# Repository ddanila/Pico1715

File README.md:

# Pico1715

An independent Pico-based replacement/expansion card for the Robotron PC 1715:
SD-backed virtual floppies, external RAM and a buffered X2 bus interface.
Original project code and design files are MIT licensed; see [LICENSE](LICENSE).

Configurable [compact triggers and rolling history](docs/analyzer-triggers.md) now
support event/address/data matching, bounded pre/post windows and USB download.

## Status

The scheduled-byte card model boots the unchanged classic ROM into SCP 0006 and
passes nine software regressions plus 36 latency/fault experiments.
See the [timing results](docs/timing-contract.md) and
[hardware requirements derived from them](hardware/timing-requirements.md).
The FPGA normal-I/O and interrupt frontend now passes all nine ROM/OS cases
in RTL co-simulation, including a shared-firmware profile with journaled SD
writeback. A 59-pin Olimex HX8K bench target is placed and routed,
and Pico Plus 2 firmware builds with PSRAM, SD CRC checking and optional journaled
writeback. See the [prototype build, wiring and parts guide](hardware/prototype.md).

**Bench prototype, not ready to manufacture:** no firmware has run on hardware,
no X2 electrical measurements have been made, and no qualified PCB exists.
The firmware co-simulator compiles the same service loop and journal code for
host execution and connects them to the board-level RTL. GPIO, time, PSRAM and
SD blocks are simulated; this does not execute RP2350 instructions or qualify
physical timing. See [firmware co-simulation](docs/firmware-cosim.md) and
[delayed storage, reset and recovery qualification](docs/firmware-storage-faults.md).

The standalone [analyzer transport](docs/analyzer-transport.md) now joins passive
FPGA cycle capture to a CRC-protected Pico link and a bounded 7 MiB PSRAM buffer.
Shared-firmware/RTL tests cover stalls, corruption, retry and buffer exhaustion;
stock-boot replay retains all 215,848 selected records. [USB control/download](docs/analyzer-usb.md)
now provides explicit arm/stop and validated capture files through a Python host
utility. A separate [passive analyzer adapter](hardware/analyzer-interface/README.md)
now has a checked schematic, full input harness and routed HX8K bitstream.
A [combined carrier schematic](hardware/carrier/README.md) now provides one
wiring contract for both personalities, a physical passive-mode interlock,
Pico power isolation, SD and button/SAFE-LED support. Both new FPGA targets route
with passing internal timing. Physical assembly, USB/timing qualification and
PCB layout remain open.

An experimental third [combined controller/capture personality](docs/combined-mode.md)
now runs disk service and finite analyzer capture concurrently. Classic CP/M guest
write/cold-read tests preserve existing files, and the HX8K build meets its
internal clock constraints. Capture loss under load is explicitly reported.
The optional [reserve supervisor](docs/reserve-interface.md) uses PIM724 SP/CE
GPIO32/33/36 and defaults to zero qualified energy. See the
[Rev A order gates](docs/rev-a-release.md) for remaining PCB work.

The first compatibility target is the **ordinary PC 1715**, retaining its boot
ROM and operating-system floppy routines. It must not be confused with the
**1715W/M**: the existing DAC emulator and available S550/TOS/M reference boot
exercise the latter's 8272-based controller. They are useful infrastructure,
not evidence that the ordinary 1715 controller has been implemented.
The owner's MB001 inventory identifies an ordinary 1715. Its board revision,
connector orientation and electrical behavior still require physical verification.

## Run the existing emulator baseline

Requirements: Python 3.10+, a C11 compiler, Git, and the external
[dac-emulation](https://github.com/ddanila/dac-emulation) checkout at the revision
recorded in [sources.json](docs/sources.json). No Python packages are required.

```sh
python3 tools/capture_dac.py \
  --dac ../dac-emulation \
  --rom ../dac/public/media/robotron/s550.bin \
  --prom ../dac/public/media/robotron/cas.bin \
  --disk ../dac/public/media/robotron/tosm10.img \
  --out local/wm-baseline
python3 -m unittest discover -s tests -v
```

The tool builds its adapter and the external emulator in this project's ignored
`build/` directory. It requires the pinned revision and clean tracked dependency
files. Inputs are read-only; the output directory must not already exist.
It records input hashes, emulator identity, I/O and interrupt-acknowledge events,
a text screen, and a report. It exits unsuccessfully if the boot prompt is absent,
inputs change, or the trace is truncated. ROM and disk contents are not committed.
Even the local trace can contain guest data: it stays ignored by default.

This is an **observational W/M baseline**, not co-simulation with Pico1715.
Read/write events can repeat on consecutive emulated CPU ticks; they are not
necessarily distinct bus transactions. Timestamps are emulator scheduling ticks,
not qualified physical X2 signal edges.

[Controller USB](docs/controller-usb.md) provides status and safe eject without
a debugger, including initialization/storage diagnostics and a host CLI.

## Next milestones

The [roadmap](docs/roadmap.md) separates implemented desk work from hardware
qualification. Safe eject/reserve-aware shutdown, motherboard interrupt-chain
modelling, firmware cost/fault tests, and controller USB status/eject are implemented
and tested within their documented simulation limits.

Analyzer capture, filtering, triggers, PSRAM transport, USB download and decoding
are also implemented. The [combined carrier](hardware/carrier/README.md) has checked
controller/analyzer FPGA personalities and a physical passive-mode interlock.
[Remote-reset software](docs/analyzer-reset.md) exists for the optional standalone
accessory; that accessory remains electrically unqualified and is disabled on the
combined carrier because GP22 serves SD chip select. X1/X2's reset contact alone
does not reset the CPU on the documented motherboard.

The [carrier layout](hardware/carrier/mechanics.md) now has local bypass placement,
2,206 routed segments, 426 vias and ground pours on both copper layers. All placed
non-SD terminals are connected. KiCad DRC reports zero violations and **12 open
connections, all involving the held SD socket**. X2 remains unplaced. See the
[routing evidence](hardware/carrier/routing.md). This is not a fabrication release;
SD/X2 geometry, return-path and timing review, optional backup power, broader OS
coverage and physical tests remain open.

Physical milestones remain:

1. Assemble the selected bench modules and verify PSRAM, SD and FPGA programming.
2. Measure worst-case Pico mailbox latency and translated bus timing on a fixture.
3. Verify X2 orientation, priority-chain wiring and mechanics on the actual 1715;
   boot the unchanged ROM and repeat the read/write/persistence tests.
4. Freeze the schematic, route the PCB, run ERC/DRC, and review manufacturing
   outputs; qualify assembled prototypes before declaring RTM.

See [hardware requirements](hardware/requirements.md),
[modelling plan](docs/modelling.md), [classic controller contract](docs/classic-controller.md)
and [licensing/provenance](NOTICE.md). The initial passing W/M run is recorded in
[reports/wm-baseline.json](reports/wm-baseline.json); local reference identities
are listed in [docs/local-evidence.json](docs/local-evidence.json).

## Plain PC1715 model

The pinned DAC revision supplies `machines/robotron1715` (runtime kind 3) with
64 KB RAM, the original ROM overlay and native card callbacks. This repository's
`model/controller.c` attaches to it without changing the emulator or guest code.
The runner enables onboard CTC/SIO, feeds completed keyboard bytes into the SIO
receive FIFO and reads the text screen from RAM. See the
[stock-software qualification](docs/onboard-keyboard.md). Production firmware
uses a bounded [two-byte receive queue](docs/receive-elasticity.md) to handle
index/mark interrupt overlap; the standalone reference model defaults to one byte.
[Service-cost tests](docs/service-costs.md) now cover processing stalls, shared-lock
contention, watchdog release and recovery during SD writeback.
[Stock Z80 cost experiments](docs/cpu-service-costs.md) combine these delays with
boot, BDOS and persistence checks, preserving both passing and overloaded profiles.
[Receive read-ahead](docs/read-ahead.md) moves byte preparation into idle mailbox
time while retaining the same two-byte capacity.
[Transmit staging](docs/transmit-staging.md) acknowledges bounded byte capture
before processing, preserving serializer deadlines and CRC validation.
[Combined stress](docs/combined-stress.md) adds deterministic processing bursts,
variable SD write latency and index-interrupt offsets, with overload and remount checks.
[Interrupt fault isolation](docs/interrupt-fault-isolation.md) releases failed
controller IRQ ownership and bypasses the chain until reset.

```sh
make test
python3 tools/check_classic.py \
  --dac ../dac-emulation \
  --rom /path/r1715bt.bin \
  --disk /path/r1715.cpm \
  --out local/classic-check
```

The checker requires the ROM and SCP image hashes recorded in
[local-evidence.json](docs/local-evidence.json), and a fresh output directory.
Inputs are read-only; writes affect disposable copies. It tests original-image
boot/DIR, SAVE, persistence, a disk-loaded BDOS read/write workload, TYPE after
cold boot, deletion/persistence, write protection, and absent media. Model-only
contract tests also cover malformed writes and interrupt/reset behavior.

See [reports/classic-compatibility.json](reports/classic-compatibility.json) and
[the controller contract and remaining gaps](docs/classic-controller.md).
Use `--timed` for scheduled bytes, or `tools/check_timing.py` with the same
arguments for the full timing suite.
**Scheduled bytes are not an electrically qualified hardware design.** Generic
PIO modes, full motherboard peripherals, other formats and physical bus behavior
remain outside this qualification.

## Bench adapter and fixture

The [buffered adapter schematic](hardware/interface/README.md) includes hardware
output gating and dual-rail supervision. The [standalone FPGA/Pico fixture](hardware/bench-fixture.md)
checks 515 mailbox transactions, IRQ/vector/RETI and returns a UART result.
Both are bench artifacts: [X2 common contacts](hardware/x2-pinout.md) are now
source-checked and assigned, including original-controller IRQ direction. Physical
validation and connector footprint selection remain pending.

The [four-contact EFS test fixture](hardware/efs58-coupon/README.md) provides
printed holder STL/STEP files, a routed passive breakout PCB and fabrication
files. It lets us screen a modern loose socket before committing to a full
58-contact replacement. Mating fit still requires sacrificial-contact trials.

## Prototype validation

```sh
make test test-store test-frontend test-irq test-pico-top lint-frontend
python3 tools/check_classic.py --cosim --dac ../dac-emulation \
  --rom /path/r1715bt.bin --disk /path/r1715.cpm --out local/rtl-check
```

RTL co-simulation requires Verilator and a C++ compiler. See
[reports/rtl-compatibility.json](reports/rtl-compatibility.json) for the nine-case
result and source hashes, and [the prototype guide](hardware/prototype.md) for
FPGA and firmware builds. ROMs and disk images remain external.

The [classic 1715 trace decoder](docs/analyzer-decoder.md) provides controller
timelines, field CRC checks, configurable WAIT/gap diagnostics and reference
comparison for downloaded compact captures.

[Safe eject and shutdown](docs/shutdown.md) now drain the journal before reporting
safe, with optional reserve-gated writeback and deterministic outage tests.

[Motherboard interrupt-chain tests](docs/motherboard-interrupts.md) now exercise
the real controller with CTC/SIO priority, IM2 vectors, RETI and card isolation.

The latest [desk-work pass](docs/desk-completion.md) adds a provisional routed
58-contact X2 breakout, assembly/probe documentation, return-path screening with
23 extra ground stitches, and a 30-case external-media survey/persistence suite.
The separate [four-layer Rev A](hardware/carrier-reva/README.md) now uses the
drawing-checked Würth SD socket and host header, with zero ERC/DRC violations
and zero opens. Return-path closure, final manufacturing review, actual connector
fit and hardware qualification remain open.

Further desk work now includes [W-loader diagnosis](docs/boot-image-diagnosis.md),
[indexed multi-extent and disk-full tests](docs/pattern-media.md) on native and
shared-firmware/FPGA backends, and an [optional reserve-power schematic](hardware/backup-power/README.md).
The reserve remains a draft with no GPIO integration or measured hold-up guarantee.

The [browser workstation](docs/browser-workstation.md) builds model and firmware/RTL
WebAssembly sessions for the classic-1715 DAC museum exhibit.

[Session capture](docs/session-capture.md) connects both emulator backends to the
workbench. The [guided bring-up runner](docs/bringup-runner.md) collects staged,
hash-bound evidence; simulated rehearsal never qualifies hardware.

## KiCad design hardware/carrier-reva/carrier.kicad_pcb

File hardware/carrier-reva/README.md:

# Rev A carrier engineering candidate

**Not for fabrication or connection to a 1715.** This directory is a separate
four-layer development candidate. The reviewed two-layer baseline remains in
`../carrier`. No physical validation is claimed.

The electrical ECO replaces the unplaced X2 schematic symbol with J6, a 60-pin
2.54 mm keyed IDC header candidate, and adds J7 for optional reserve power.
All 76 schematic components are placed. ERC and DRC are checked afresh by the
CAD target. The SD socket is now Würth 693071010811, with all connections closed.
J6 uses the exact 61206021621 drawing dimensions, including 1.10 mm holes.
J7's 0.95 mm finished holes match the JST 0.90–1.00 mm reference range.
See `sd-replacement-review.md` and `connector-review.json` for sources and limits.
Drawing checks do not claim physical fit or signal-integrity qualification.

## Harness and power

Use a straight-through keyed 60-conductor cable, maximum 100 mm, to a separate
EFS58 adapter. The **electrical** assignment is A1→1, B1→2, … A29→57,
B29→58; pins 59 and 60 are NC. Every contact, including existing unused
contacts, is in `connections.json`. This mapping is not a claim about the
EFS contact fit. J6 top-view pin 1 is at (60,215), pin 2 at
(60,212.46); the key faces south, toward the odd row. The mate-facing view
is mirrored: assemble by pin numbers and verify continuity before use. Do not infer orientation
from a mirrored photograph or wire-colour convention.

J7 is a power connector, not a status/GPIO port:

| Pin | Net | Function |
| --- | --- | --- |
| 1 | GND | Common return |
| 2 | V5_MODULE | Raw module supply |
| 3 | P_VSYS | Backed Pico supply |

Keep D1 fitted. Leave J7 empty for the initial assembly; the reserve daughterboard
is not included in the first order. Never jumper pins 2 and 3 as an improvised
reserve bypass. The normal D1 feed already supports operation without reserve.
Reserve status uses Pico SP/CE GP32/33/36 separately; the firmware supervisor
must not report a protected write budget without measured hold-up evidence.

## Layout and validation

The candidate is 160 × 210 mm. F.Cu/B.Cu carry signals and power; In1.Cu/In2.Cu
are GND. The proposed 1.6 mm ENIG stack-up targets JLC04161H-7628 but remains
subject to supplier confirmation. The SD body exclusion applies only to F.Cu.
Existing outer copper is retained; the routing workflow defaults to removing
F_CLK and F_WR_N for re-routing and adds the host/reserve connections. Repeat
`--replace-net NET` to select other nets without disturbing previously replaced
routes. Router output is
never itself sign-off evidence.

- `make test-carrier-reva`: portable net parity and interface mutation tests.
- `make test-carrier-reva-cad`: fresh schematic export, ERC and DRC review.
  It explicitly permits and **reports** open connections; it is not an order gate.
- `python3 tools/package_carrier_reva.py --out local/reva-review-<unique-name>`:
  freshly checked, hashed engineering review ZIP. No order Gerbers are included.
- `/usr/bin/python3 tools/prepare_carrier_reva_routing.py --out local/reva-router`:
  outer-layer router input with SD present and ground excluded.
- `/usr/bin/python3 tools/import_carrier_reva_routing.py local/reva-router local/reva-routes.json`:
  candidate additions from `carrier.ses`; import into the generator with
  `--routes`, then refill/check independently before adoption.

Regenerate the schematic with `python3 tools/generate_carrier_reva.py`, export
its netlist with KiCad's `kicadxml` format, then generate the PCB with
`/usr/bin/python3 tools/generate_carrier_reva_pcb.py`. The board generator needs
KiCad 10's system Python module. It uses the checked-in `routes.json` by default. `--base-only` explicitly
creates the uncompleted placement candidate. `--routes` selects a different
candidate for review. The checked `placement-overrides.json` moves only C19;
connector/module positions and mounting holes stay fixed.

All 408 signal vias now meet the 4 mm return target, and planar assembly/plane
gap desk review is recorded in `assembly-review.json`. A fabrication release
has independently inspected exports bound by hashes; release still requires supplier acceptance and a
postcode-specific delivered Estonia quote. Physical EFS fit, power isolation, signal integrity and functional
bring-up remain later gates. Assemble and test one board before populating four
more. CPU RESET2 remains an input, not a board-driven CPU reset output.

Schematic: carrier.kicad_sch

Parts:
C1, C2, C3, C4, C5, C6, C7, C8, C9, C10, C11, C12, C13, C14, C15, C16, C17, C18, C19: 100nF; C_0805_2012Metric
C20, C21, C22: 10uF_10V; C_0805_2012Metric
D1: SS14; D_SMA
EXT1: OLIMEX_EXT1; PinHeader_2x20_P1.27mm_Vertical
EXT2: OLIMEX_EXT2; PinHeader_2x20_P1.27mm_Vertical
EXT3: OLIMEX_EXT3; PinHeader_2x20_P1.27mm_Vertical
ISO1, ISO2, ISO3: SN74CB3Q3245PWR; TSSOP-20_4.4x6.5mm_P0.65mm
J1: PGM1_PIN5_CDONE_TAP; PinHeader_1x02_P2.54mm_Vertical
J2: PIM724_PICO_PLUS2; PIM724_SocketPair
J3: 693071010811; microSD_Wuerth_693071010811
J4: REGULATED_5V_INPUT; JST_XH_B2B-XH-A_1x02_P2.50mm_Vertical
J5: BRINGUP_PROBES; PinHeader_1x15_P2.54mm_Vertical
J6: 61206021621_HOST_HARNESS; IDC_Wuerth_61206021621
J7: B3B-XH-A_RESERVE_POWER; JST_XH_B3B-XH-A_1x03_P2.50mm_Vertical
R1, R3, R5: 2k2; R_0805_2012Metric
R2, R4, R6: 22k; R_0805_2012Metric
R7, R8, R9, R10, R11, R12, R13, R17, R19, R20, R21: 4k7; R_0805_2012Metric
R14, R15: 1k; R_0805_2012Metric
R16: 100k; R_0805_2012Metric
R18: 10k; R_0805_2012Metric
R22, R23, R24: 47k; R_0805_2012Metric
RX1, RX2, RX3, RX4, RX5: SN74LVC541ADWR; SOIC-20W_7.5x12.8mm_P1.27mm
SW1: JS202011JCQN; JS202011JCQN_VendorPins
U4: SN74AHCT541DWR; SOIC-20W_7.5x12.8mm_P1.27mm
U5: SN74AHCT1G125DBVR; SOT-23-5
U6, U7: SN74LVC08ADR; SOIC-14_3.9x8.7mm_P1.27mm
U8, U13: SN74LVC00ADR; SOIC-14_3.9x8.7mm_P1.27mm
U9: SN74LVC07ADR; SOIC-14_3.9x8.7mm_P1.27mm
U10, U12: TLV803EA30DBZR; SOT-23
U11: TLV803EA46DBZR; SOT-23

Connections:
/ARMED: J5.9 (ARMED), U7.11 (4Y), U8.1 (1A), U8.4 (2A), U8.9 (3A), U8.12 (4A), U8.13 (4B)
/BACKEND_OK: U7.6 (2Y), U7.9 (3A)
/CDONE: J1.1 (CDONE_FROM_PGM1_5), J5.5 (CDONE), R16.1, U6.10 (3B)
/DATA_EN_N: U8.3 (1Y), U9.1 (1A)
/DATA_OE_N: J5.10 (DATA_OE_N), R14.2, U4.19 (OE2_N), U9.2 (1Y)
/DRIVEN_IEO: SW1.7 (CONTROLLER_IEO), U5.4 (Y)
/F_A0: EXT1.7 (F_A0), RX1.18 (Y0)
/F_A1: EXT1.9 (F_A1), RX1.17 (Y1)
/F_A2: EXT1.11 (F_A2), RX1.16 (Y2)
/F_A3: EXT1.13 (F_A3), RX1.15 (Y3)
/F_A4: EXT1.15 (F_A4), RX1.14 (Y4)
/F_A5: EXT1.17 (F_A5), RX1.13 (Y5)
/F_A6: EXT1.19 (F_A6), RX1.12 (Y6)
/F_A7: EXT1.21 (F_A7), RX1.11 (Y7)
/F_A8: EXT2.15 (F_A8), RX2.18 (Y0)
/F_A9: EXT2.17 (F_A9), RX2.17 (Y1)
/F_A10: EXT2.19 (F_A10), RX2.16 (Y2)
/F_A11: EXT2.21 (F_A11), RX2.15 (Y3)
/F_A12: EXT2.23 (F_A12), RX2.14 (Y4)
/F_A13: EXT2.25 (F_A13), RX2.13 (Y5)
/F_A14: EXT2.27 (F_A14), RX2.12 (Y6)
/F_A15: EXT2.29 (F_A15), RX2.11 (Y7)
/F_BAO_N: EXT2.40 (F_BAO_N), RX5.15 (Y3)
/F_BUSRQ_N: EXT2.39 (F_BUSRQ_N), RX5.16 (Y2)
/F_CLK: EXT2.33 (F_CLK), RX4.12 (Y6)
/F_D0: EXT1.23 (F_D0), RX3.18 (Y0)
/F_D1: EXT1.25 (F_D1), RX3.17 (Y1)
/F_D2: EXT1.27 (F_D2), RX3.16 (Y2)
/F_D3: EXT1.29 (F_D3), RX3.15 (Y3)
/F_D4: EXT1.31 (F_D4), RX3.14 (Y4)
/F_D5: EXT1.33 (F_D5), RX3.13 (Y5)
/F_D6: EXT1.35 (F_D6), RX3.12 (Y6)
/F_D7: EXT1.37 (F_D7), RX3.11 (Y7)
/F_DO0: EXT1.39 (F_DO0), U4.2 (A0)
/F_DO1: EXT1.40 (F_DO1), U4.3 (A1)
/F_DO2: EXT1.38 (F_DO2), U4.4 (A2)
/F_DO3: EXT1.36 (F_DO3), U4.5 (A3)
/F_DO4: EXT1.34 (F_DO4), U4.6 (A4)
/F_DO5: EXT1.32 (F_DO5), U4.7 (A5)
/F_DO6: EXT1.30 (F_DO6), U4.8 (A6)
/F_DO7: EXT1.28 (F_DO7), U4.9 (A7)
/F_FAULT: EXT2.13 (F_FAULT), J5.13 (F_FAULT)
/F_HOST_OE: EXT1.10 (F_HOST_OE), R10.1, U8.2 (1B)
/F_IEO: EXT2.11 (F_IEO), R13.1, U5.2 (A)
/F_INT: EXT2.9 (F_INT), R12.1, U8.10 (3B)
/F_INT_N: EXT2.37 (F_INT_N), RX5.17 (Y1)
/F_IORQ_N: EXT1.26 (F_IORQ_N), RX4.17 (Y1)
/F_M1_N: EXT1.24 (F_M1_N), RX4.14 (Y4)
/F_MREQ_N: EXT1.22 (F_MREQ_N), RX4.18 (Y0)
/F_PRIORITY: EXT1.16 (F_PRIORITY), RX5.14 (Y4)
/F_RD_N: EXT1.20 (F_RD_N), RX4.16 (Y2)
/F_RESET_N: EXT1.14 (F_RESET_N), ISO2.9 (A7), RX4.11 (Y7), U7.10 (3B)
/F_RFSH_N: EXT2.31 (F_RFSH_N), RX4.13 (Y5)
/F_WAIT: EXT2.7 (F_WAIT), R11.1, U8.5 (2B)
/F_WAIT_N: EXT2.35 (F_WAIT_N), RX5.18 (Y0)
/F_WR_N: EXT1.18 (F_WR_N), RX4.15 (Y3)
/GND: C1.2, C2.2, C3.2, C4.2, C5.2, C6.2, C7.2, C8.2, C9.2, C10.2, C11.2, C12.2, C13.2, C14.2, C15.2, C16.2, C17.2, C18.2, C19.2, C20.2, C21.2, C22.2, EXT1.2 (GND), EXT1.4 (GND), EXT1.8 (GND), EXT2.2 (GND), EXT2.4 (GND), EXT2.8 (GND), EXT3.2 (GND), EXT3.4 (GND), EXT3.8 (GND), ISO1.10 (GND), ISO2.10 (GND), ISO3.10 (GND), J1.2 (GND), J2.3 (GND), J2.8 (GND), J2.13 (GND), J2.18 (GND), J2.23 (GND), J2.28 (GND), J2.33 (GND), J2.38 (GND), J3.6 (VSS), J4.2 (GND), J5.1 (GND), J6.1 (0V), J6.2 (0V), J6.3 (0V), J6.4 (0V), J7.1 (GND), R2.2, R4.2, R6.2, R7.2, R8.2, R9.2, R10.2, R11.2, R12.2, R13.2, R16.2, R19.2, R20.2, RX1.1 (OE1_N), RX1.10 (GND), RX1.19 (OE2_N), RX2.1 (OE1_N), RX2.10 (GND), RX2.19 (OE2_N), RX3.1 (OE1_N), RX3.10 (GND), RX3.19 (OE2_N), RX4.1 (OE1_N), RX4.10 (GND), RX4.19 (OE2_N), RX5.1 (OE1_N), RX5.7 (A5), RX5.8 (A6), RX5.9 (A7), RX5.10 (GND), RX5.19 (OE2_N), SW1.1 (PASSIVE_GND), U4.1 (OE1_N), U4.10 (GND), U5.3 (GND), U6.7 (GND), U7.7 (GND), U8.7 (GND), U9.7 (GND), U10.1 (GND), U11.1 (GND), U12.1 (GND), U13.4 (2A), U13.5 (2B), U13.7 (GND), U13.9 (3A), U13.10 (3B), U13.12 (4A), U13.13 (4B)
/H_A0: J6.37 (AB0), RX1.2 (A0)
/H_A1: J6.38 (AB1), RX1.3 (A1)
/H_A2: J6.35 (AB2), RX1.4 (A2)
/H_A3: J6.36 (AB3), RX1.5 (A3)
/H_A4: J6.33 (AB4), RX1.6 (A4)
/H_A5: J6.34 (AB5), RX1.7 (A5)
/H_A6: J6.31 (AB6), RX1.8 (A6)
/H_A7: J6.32 (AB7), RX1.9 (A7)
/H_A8: J6.27 (AB8), RX2.2 (A0)
/H_A9: J6.28 (AB9), RX2.3 (A1)
/H_A10: J6.25 (AB10), RX2.4 (A2)
/H_A11: J6.26 (AB11), RX2.5 (A3)
/H_A12: J6.23 (AB12), RX2.6 (A4)
/H_A13: J6.24 (AB13), RX2.7 (A5)
/H_A14: J6.21 (AB14), RX2.8 (A6)
/H_A15: J6.22 (AB15), RX2.9 (A7)
/H_BAO_N: J6.53 (/BAO), RX5.5 (A3)
/H_BUSRQ_N: J6.40 (/BUSRQ), RX5.4 (A2)
/H_CLK: J6.41 (TAKT-X2), RX4.8 (A6)
/H_D0: J6.14 (DB0), RX3.2 (A0), U4.18 (Y0)
/H_D1: J6.13 (DB1), RX3.3 (A1), U4.17 (Y1)
/H_D2: J6.12 (DB2), RX3.4 (A2), U4.16 (Y2)
/H_D3: J6.11 (DB3), RX3.5 (A3), U4.15 (Y3)
/H_D4: J6.10 (DB4), RX3.6 (A4), U4.14 (Y4)
/H_D5: J6.9 (DB5), RX3.7 (A5), U4.13 (Y5)
/H_D6: J6.8 (DB6), RX3.8 (A6), U4.12 (Y6)
/H_D7: J6.7 (DB7), RX3.9 (A7), U4.11 (Y7)
/H_INT_N: J5.12 (H_INT_N), J6.46 (/INT), RX5.3 (A1), U9.6 (3Y)
/H_IORQ_N: J6.48 (/IORQ), RX4.3 (A1)
/H_M1_N: J6.51 (/M1), RX4.6 (A4)
/H_MREQ_N: J6.17 (/MREQ), RX4.2 (A0)
/H_PRIORITY: J6.20 (IEO), R18.2, RX5.6 (A4), SW1.5 (PASSIVE_IEI)
/H_PRIORITY_OUT: J6.19 (IEI), SW1.6 (COMMON_IEO)
/H_RD_N: J6.16 (/RD), RX4.4 (A2)
/H_RESET_N: J6.39 (/RESET), RX4.9 (A7)
/H_RFSH_N: J6.49 (/RFSH), RX4.7 (A5)
/H_WAIT_N: J5.11 (H_WAIT_N), J6.47 (/WAIT), RX5.2 (A0), U9.4 (2Y)
/H_WR_N: J6.15 (/WR), RX4.5 (A3)
/IEO_EN_N: U8.11 (4Y), U9.9 (4A)
/IEO_OE_N: R15.2, U5.1 (OE_N), U9.8 (4Y)
/INT_EN_N: U8.8 (3Y), U9.5 (3A)
/LINK_OE_N: ISO1.19 (OE_N), ISO2.19 (OE_N), ISO3.19 (OE_N), R17.2, U13.3 (1Y)
/LINK_OK: EXT3.29 (LINK_OK), J5.8 (LINK_OK), U6.8 (3Y), U6.13 (4B), U13.1 (1A), U13.2 (1B)
/L_GP0: EXT2.28 (L_GP0), ISO1.2 (A0)
/L_GP1: EXT2.26 (L_GP1), ISO1.3 (A1)
/L_GP2: EXT2.24 (L_GP2), ISO1.4 (A2)
/L_GP3: EXT2.22 (L_GP3), ISO1.5 (A3)
/L_GP4: EXT2.20 (L_GP4), ISO1.6 (A4)
/L_GP5: EXT2.18 (L_GP5), ISO1.7 (A5)
/L_GP6: EXT2.16 (L_GP6), ISO1.8 (A6)
/L_GP7: EXT2.14 (L_GP7), ISO1.9 (A7)
/L_GP8: EXT2.12 (L_GP8), ISO2.2 (A0)
/L_GP9: EXT2.10 (L_GP9), ISO2.3 (A1)
/L_GP10: EXT3.7 (L_GP10), ISO2.4 (A2)
/L_GP11: EXT3.9 (L_GP11), ISO2.5 (A3)
/L_GP12: EXT3.11 (L_GP12), ISO2.6 (A4)
/L_GP13: EXT3.13 (L_GP13), ISO2.7 (A5)
/L_GP14: EXT3.15 (L_GP14), ISO2.8 (A6), R19.1
/L_GP16: EXT3.17 (L_GP16), ISO3.2 (A0), R20.1
/L_GP17: EXT3.19 (L_GP17), ISO3.3 (A1), R21.1
/L_GP18: EXT3.21 (L_GP18), ISO3.4 (A2)
/L_GP19: EXT3.23 (L_GP19), ISO3.5 (A3)
/L_GP20: EXT3.25 (L_GP20), ISO3.6 (A4)
/L_GP21: EXT3.27 (L_GP21), ISO3.7 (A5), R9.1, U7.5 (2B)
/MODE_CTL: J5.6 (MODE_CTL), R7.1, SW1.2 (COMMON_MODE), U7.13 (4B)
/P3V3: C15.1, C19.1, C21.1, J2.36 (P3V3), J3.4 (VDD), J5.14 (P3V3), R5.1, R22.1, R23.1, R24.1, U12.3 (VDD)
/PERSONALITY_CTL: EXT2.38 (PERSONALITY_CTL), J5.7 (PERSONALITY_CTL), R8.1, U7.2 (1B)
/PG3: J5.2 (PG3), R1.2, R2.1, U6.1 (1A), U6.4 (2A), U10.2 (RESET_N)
/PG5: J5.3 (PG5), R3.2, R4.1, U6.2 (1B), U11.2 (RESET_N)
/PGP: J5.4 (PGP), R5.2, R6.1, U6.5 (2B), U12.2 (RESET_N)
/POWERED: U6.11 (4Y), U7.1 (1A)
/POWER_GOOD: EXT1.12 (POWER_GOOD), U6.3 (1Y), U6.12 (4A)
/P_GP0: ISO1.18 (B0), J2.1 (P_GP0)
/P_GP1: ISO1.17 (B1), J2.2 (P_GP1)
/P_GP2: ISO1.16 (B2), J2.4 (P_GP2)
/P_GP3: ISO1.15 (B3), J2.5 (P_GP3)
/P_GP4: ISO1.14 (B4), J2.6 (P_GP4)
/P_GP5: ISO1.13 (B5), J2.7 (P_GP5)
/P_GP6: ISO1.12 (B6), J2.9 (P_GP6)
/P_GP7: ISO1.11 (B7), J2.10 (P_GP7)
/P_GP8: ISO2.18 (B0), J2.11 (P_GP8)
/P_GP9: ISO2.17 (B1), J2.12 (P_GP9)
/P_GP10: ISO2.16 (B2), J2.14 (P_GP10)
/P_GP11: ISO2.15 (B3), J2.15 (P_GP11)
/P_GP12: ISO2.14 (B4), J2.16 (P_GP12)
/P_GP13: ISO2.13 (B5), J2.17 (P_GP13)
/P_GP14: ISO2.12 (B6), J2.19 (P_GP14)
/P_GP15: ISO2.11 (B7), J2.20 (P_GP15)
/P_GP16: ISO3.18 (B0), J2.21 (P_GP16)
/P_GP17: ISO3.17 (B1), J2.22 (P_GP17)
/P_GP18: ISO3.16 (B2), J2.24 (P_GP18)
/P_GP19: ISO3.15 (B3), J2.25 (P_GP19)
/P_GP20: ISO3.14 (B4), J2.26 (P_GP20)
/P_GP21: ISO3.13 (B5), J2.27 (P_GP21)
/P_GP22: J2.29 (P_GP22), J3.2 (DAT3_CS), R22.2
/P_GP26: J2.31 (P_GP26), J3.5 (CLK)
/P_GP27: J2.32 (P_GP27), J3.3 (CMD_MOSI)
/P_GP28: J2.34 (P_GP28), J3.7 (DAT0_MISO)
/P_VSYS: D1.1 (K), J2.39 (P_VSYS), J7.3 (BACKED_VSYS)
/QUALIFIED: U7.3 (1Y), U7.4 (2A)
/RAILS_OK: U6.6 (2Y), U6.9 (3A)
/RESET_OK: U7.8 (3Y), U7.12 (4A)
/SD_DAT1: J3.8 (DAT1), R23.2
/SD_DAT2: J3.1 (DAT2), R24.2
/V3P3: C1.1, C2.1, C3.1, C4.1, C5.1, C8.1, C9.1, C10.1, C11.1, C12.1, C13.1, C16.1, C17.1, C18.1, C20.1, EXT1.3 (V3P3), ISO1.20 (VCC), ISO2.20 (VCC), ISO3.20 (VCC), J5.15 (V3P3), R1.1, R17.1, R21.2, RX1.20 (VCC), RX2.20 (VCC), RX3.20 (VCC), RX4.20 (VCC), RX5.20 (VCC), SW1.3 (CONTROLLER_3V3), U6.14 (VCC), U7.14 (VCC), U8.14 (VCC), U9.11 (5A), U9.13 (6A), U9.14 (VCC), U10.3 (VDD), U13.14 (VCC)
/V5_HOST: C6.1, C7.1, C14.1, J6.57 (5P), J6.58 (5P), R3.1, R14.1, R15.1, R18.1, U4.20 (VCC), U5.5 (VCC), U11.3 (VDD)
/V5_MODULE: C22.1, D1.2 (A), EXT1.1 (V5_MODULE), J4.1 (5V), J7.2 (RAW_5V)
/WAIT_EN_N: U8.6 (2Y), U9.3 (2A)

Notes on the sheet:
Pico1715 Rev A / FOUR-LAYER CANDIDATE / NOT FOR FABRICATION
J6: straight-through 60-pin host harness; A=odd, B=even; 59/60 NC. Separate unqualified EFS58 adapter.
J7 reserve POWER only: 1 GND, 2 raw module 5V, 3 backed VSYS. Keep D1 fitted; optional daughter not included.
SD and connector drawing geometry checked; physical fit untested. RESET2 input only. Power off before mode or cable changes.

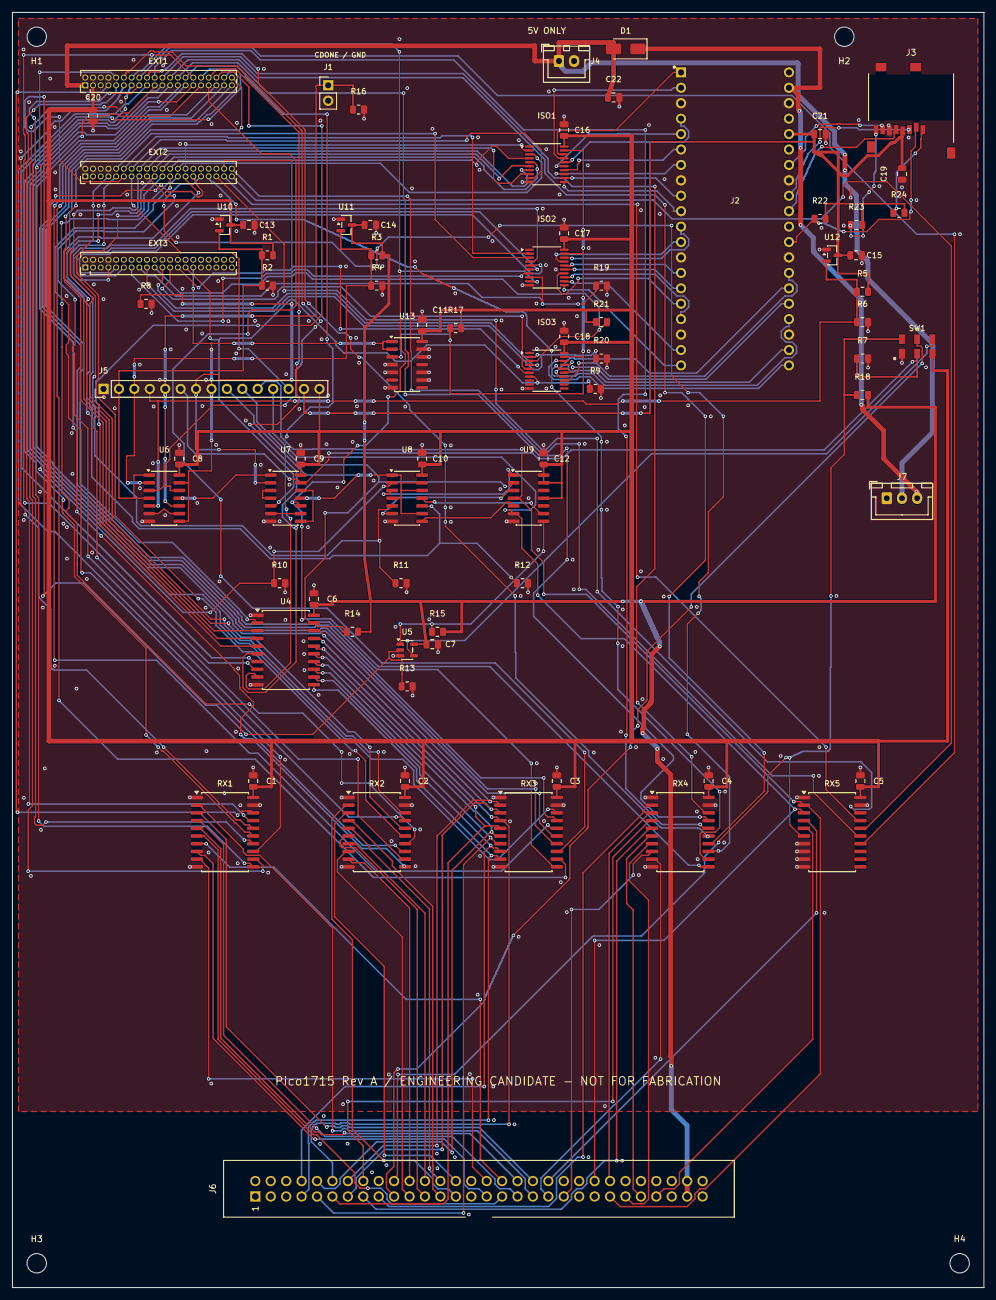
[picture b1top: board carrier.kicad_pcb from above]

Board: 4 copper layers, 160.0 x 210.0 mm, 80 parts (0 on the bottom side), 165 nets.

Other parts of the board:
H1, H2, H3, H4: MountingHole_3.2mm_M3

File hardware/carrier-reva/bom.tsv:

Reference	Value	Footprint	Datasheet
J6	61206021621_HOST_HARNESS	Pico1715_RevA:IDC_Wuerth_61206021621	https://www.we-online.com/components/products/datasheet/6120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
RX1	SN74LVC541ADWR	Package_SO:SOIC-20W_7.5x12.8mm_P1.27mm	https://www.ti.com/lit/ds/symlink/sn74lvc541a.pdf
RX2	SN74LVC541ADWR	Package_SO:SOIC-20W_7.5x12.8mm_P1.27mm	https://www.ti.com/lit/ds/symlink/sn74lvc541a.pdf
RX3	SN74LVC541ADWR	Package_SO:SOIC-20W_7.5x12.8mm_P1.27mm	https://www.ti.com/lit/ds/symlink/sn74lvc541a.pdf
RX4	SN74LVC541ADWR	Package_SO:SOIC-20W_7.5x12.8mm_P1.27mm	https://www.ti.com/lit/ds/symlink/sn74lvc541a.pdf
RX5	SN74LVC541ADWR	Package_SO:SOIC-20W_7.5x12.8mm_P1.27mm	https://www.ti.com/lit/ds/symlink/sn74lvc541a.pdf
U4	SN74AHCT541DWR	Package_SO:SOIC-20W_7.5x12.8mm_P1.27mm	https://www.ti.com/lit/ds/symlink/sn74ahct541.pdf
U5	SN74AHCT1G125DBVR	Package_TO_SOT_SMD:SOT-23-5	https://www.ti.com/lit/ds/symlink/sn74ahct1g125.pdf
U6	SN74LVC08ADR	Package_SO:SOIC-14_3.9x8.7mm_P1.27mm	https://www.ti.com/lit/ds/symlink/sn74lvc08a.pdf
U7	SN74LVC08ADR	Package_SO:SOIC-14_3.9x8.7mm_P1.27mm	https://www.ti.com/lit/ds/symlink/sn74lvc08a.pdf
U8	SN74LVC00ADR	Package_SO:SOIC-14_3.9x8.7mm_P1.27mm	https://www.ti.com/lit/ds/symlink/sn74lvc00a.pdf
U13	SN74LVC00ADR	Package_SO:SOIC-14_3.9x8.7mm_P1.27mm	https://www.ti.com/lit/ds/symlink/sn74lvc00a.pdf
U9	SN74LVC07ADR	Package_SO:SOIC-14_3.9x8.7mm_P1.27mm	https://www.ti.com/lit/ds/symlink/sn74lvc07a.pdf
U10	TLV803EA30DBZR	Package_TO_SOT_SMD:SOT-23	https://www.ti.com/lit/ds/symlink/tlv803e.pdf
U11	TLV803EA46DBZR	Package_TO_SOT_SMD:SOT-23	https://www.ti.com/lit/ds/symlink/tlv803e.pdf
U12	TLV803EA30DBZR	Package_TO_SOT_SMD:SOT-23	https://www.ti.com/lit/ds/symlink/tlv803e.pdf
SW1	JS202011JCQN	Pico1715_Carrier:JS202011JCQN_VendorPins	https://www.littelfuse.com/products/switches/slide-switches/js
ISO1	SN74CB3Q3245PWR	Package_SO:TSSOP-20_4.4x6.5mm_P0.65mm	https://www.ti.com/lit/ds/symlink/sn74cb3q3245.pdf
ISO2	SN74CB3Q3245PWR	Package_SO:TSSOP-20_4.4x6.5mm_P0.65mm	https://www.ti.com/lit/ds/symlink/sn74cb3q3245.pdf
ISO3	SN74CB3Q3245PWR	Package_SO:TSSOP-20_4.4x6.5mm_P0.65mm	https://www.ti.com/lit/ds/symlink/sn74cb3q3245.pdf
EXT1	OLIMEX_EXT1	Connector_PinHeader_1.27mm:PinHeader_2x20_P1.27mm_Vertical	-
EXT2	OLIMEX_EXT2	Connector_PinHeader_1.27mm:PinHeader_2x20_P1.27mm_Vertical	-
EXT3	OLIMEX_EXT3	Connector_PinHeader_1.27mm:PinHeader_2x20_P1.27mm_Vertical	-
J1	PGM1_PIN5_CDONE_TAP	Connector_PinHeader_2.54mm:PinHeader_1x02_P2.54mm_Vertical	-
J2	PIM724_PICO_PLUS2	Pico1715_Carrier:PIM724_SocketPair	https://shop.pimoroni.com/products/pimoroni-pico-plus-2
J3	693071010811	Pico1715_RevA:microSD_Wuerth_693071010811	https://www.we-online.com/components/products/datasheet/6930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
J4	REGULATED_5V_INPUT	Connector_JST:JST_XH_B2B-XH-A_1x02_P2.50mm_Vertical	-
D1	SS14	Diode_SMD:D_SMA	https://www.vishay.com/docs/88746/ss12.pdf
J5	BRINGUP_PROBES	Connector_PinHeader_2.54mm:PinHeader_1x15_P2.54mm_Vertical	-
R1	2k2	Resistor_SMD:R_0805_2012Metric	-
R2	22k	Resistor_SMD:R_0805_2012Metric	-
R3	2k2	Resistor_SMD:R_0805_2012Metric	-
R4	22k	Resistor_SMD:R_0805_2012Metric	-
R5	2k2	Resistor_SMD:R_0805_2012Metric	-
R6	22k	Resistor_SMD:R_0805_2012Metric	-
R7	4k7	Resistor_SMD:R_0805_2012Metric	-
R8	4k7	Resistor_SMD:R_0805_2012Metric	-
R9	4k7	Resistor_SMD:R_0805_2012Metric	-
R10	4k7	Resistor_SMD:R_0805_2012Metric	-
R11	4k7	Resistor_SMD:R_0805_2012Metric	-
R12	4k7	Resistor_SMD:R_0805_2012Metric	-
R13	4k7	Resistor_SMD:R_0805_2012Metric	-
R14	1k	Resistor_SMD:R_0805_2012Metric	-
R15	1k	Resistor_SMD:R_0805_2012Metric	-
R16	100k	Resistor_SMD:R_0805_2012Metric	-
R17	4k7	Resistor_SMD:R_0805_2012Metric	-
R18	10k	Resistor_SMD:R_0805_2012Metric	-
R19	4k7	Resistor_SMD:R_0805_2012Metric	-
R20	4k7	Resistor_SMD:R_0805_2012Metric	-
R21	4k7	Resistor_SMD:R_0805_2012Metric	-
R22	47k	Resistor_SMD:R_0805_2012Metric	-
R23	47k	Resistor_SMD:R_0805_2012Metric	-
R24	47k	Resistor_SMD:R_0805_2012Metric	-
C1	100nF	Capacitor_SMD:C_0805_2012Metric	-
C2	100nF	Capacitor_SMD:C_0805_2012Metric	-
C3	100nF	Capacitor_SMD:C_0805_2012Metric	-
C4	100nF	Capacitor_SMD:C_0805_2012Metric	-
C5	100nF	Capacitor_SMD:C_0805_2012Metric	-
C6	100nF	Capacitor_SMD:C_0805_2012Metric	-
C7	100nF	Capacitor_SMD:C_0805_2012Metric	-
C8	100nF	Capacitor_SMD:C_0805_2012Metric	-
C9	100nF	Capacitor_SMD:C_0805_2012Metric	-
C10	100nF	Capacitor_SMD:C_0805_2012Metric	-
C11	100nF	Capacitor_SMD:C_0805_2012Metric	-
C12	100nF	Capacitor_SMD:C_0805_2012Metric	-
C13	100nF	Capacitor_SMD:C_0805_2012Metric	-
C14	100nF	Capacitor_SMD:C_0805_2012Metric	-
C15	100nF	Capacitor_SMD:C_0805_2012Metric	-
C16	100nF	Capacitor_SMD:C_0805_2012Metric	-
C17	100nF	Capacitor_SMD:C_0805_2012Metric	-
C18	100nF	Capacitor_SMD:C_0805_2012Metric	-
C19	100nF	Capacitor_SMD:C_0805_2012Metric	-
C20	10uF_10V	Capacitor_SMD:C_0805_2012Metric	-
C21	10uF_10V	Capacitor_SMD:C_0805_2012Metric	-
C22	10uF_10V	Capacitor_SMD:C_0805_2012Metric	-
J7	B3B-XH-A_RESERVE_POWER	Connector_JST:JST_XH_B3B-XH-A_1x03_P2.50mm_Vertical	https://www.jst-mfg.com/product/index.php?series=277

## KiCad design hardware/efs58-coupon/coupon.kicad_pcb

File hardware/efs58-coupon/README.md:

# Four-contact EFS experiment

This is a buildable **contact test fixture**, not a replacement 202-58 connector.
It separates the uncertain spring-contact fit from the large connector body and
Pico1715 electronics. C1–C4 are fixture identifiers, **not X1/X2 pin numbers**.
Nothing here connects to power, Pico, FPGA, or the carrier.

The selected experiment uses four loose **Mill-Max 1001-0-15-15-30-27-04-0**
receptacles on a 2.5 × 2.5 mm grid. Their documented outside dimensions allow
us to design the holder now. Their round-pin rating does **not** qualify an EFS
blade; thickness alone, including the recalled 0.3 mm figure, cannot establish
that fit. Measure width, thickness and insertion length on a sacrificial EFS
male contact before inserting it. Do not use the motherboard as the first test.

## Files

* `front.stl` and one of `body_c15.stl`, `body_c25.stl`, `body_c35.stl`:
  print-ready parts in millimetres, minimum Z at the print bed. Suffixes are
  **diametral** clearances above nominal socket diameters: 0.15/0.25/0.35 mm.
* Matching STEP files preserve assembly Z coordinates; `assembly.step` includes
  the nominal socket envelopes and PCB slab. Socket springs are not modelled.
* `coupon.kicad_sch`, `coupon.kicad_pcb`, local symbol/footprint libraries:
  four isolated routed paths on a 28 × 30 mm, two-layer, 1.6 mm FR4 board.
* `fabrication/`: Gerbers and separate plated/non-plated Excellon drills for
  **this test PCB only**. No production carrier order is implied.
* `parameters.json`: sourced contact dimensions and our design choices.
  `cad-checks.json` records solid and mesh checks; `validation.json` records
  checked file hashes. `measurements.csv` is an intentionally blank bench log.
* `drawing.svg`: orientation, stack and assembly instructions.

## Why this contact

| Candidate | Evidence and decision |
| --- | --- |
| Loose Mill-Max 1001, #30 contact | **Selected for experiment.** Published geometry, straight solder tail, individual small-quantity stock listing; no special crimp tool. Flat-blade compatibility still unknown. |
| Harwin M20-1180042 / generic Dupont | M20 specifies a 0.64 mm square mating pin. Generic parts have no controlled spring geometry. Not evidence of grip on a thin EFS blade. |
| Harwin M80-013 | Documented 0.46–0.51 mm round-pin system; crimp tooling adds expense without resolving blade compatibility. |
| DIN 41612 donor | A modified DIN male fitting an EFS female does not prove the reverse pairing. Tail dimensions such as 0.3 mm are not a female mating specification. |
| Original EFS female donor | Best baseline for comparison. Exact contact retention and extraction must be measured; do not assume EFS26 and EFS58 contacts have identical retention bodies. |

Sources: [Mill-Max manufacturer's metric catalogue](https://www.mill-max.com/sites/default/files/external/catalog/2021-02/153M-201M.pdf),
printed p165 / PDF p17; [Harwin M20](https://www.harwin.com/products/M20-1180042);
[Harwin M80 drawing](https://cdn.harwin.com/pdfs/M80-013.pdf).
The EFS 2.5 mm mating grid comes from TGL 29331/03, p2 Fig.1; the original
angled female has **5 mm PCB-tail spacing**, which this straight test fixture
does not reproduce. See the [EFS evidence review](../carrier/efs58/investigation.md).
Source PDF SHA-256 for the Mill-Max catalogue:
`ca75ed3c0f2ca1b360a38616e2883a8fcdfbfc3defccbdc877a0b3c76338f663`.
Original CAD/code are MIT; manufacturer documents remain with their owners.

## Small shopping list

| Item | Quantity | Notes |
| --- | ---: | --- |
| Mill-Max 1001-0-15-15-30-27-04-0 | 10 | Four installed, six for single-contact trials/spares |
| M2 × 12 mm machine screws | 2 | With four small washers and two nuts; tighten lightly |
| Printed front | 1 | Non-conductive, tough resin preferred |
| Printed bodies | 3 | One of each clearance for calibration; only one assembled |
| Coupon PCB | 1 | 1.6 mm FR4, standard two-layer service; no assembly stencil needed |
| Thin insulated hookup wire | 4 lengths | Optional test leads soldered to TP1–TP4 |
| Sacrificial original EFS male contacts and known-good female | A few | Grip/depth reference; do not destroy a working rare board |

On 2026-10-26, the [Mouser listing](https://www.mouser.com/ProductDetail/Mill-Max/1001-0-15-15-30-27-04-0)
returned small-quantity stock and USD 0.68 each / USD 5.91 for ten. This is a
research snapshot, not an Estonia VAT/shipping-inclusive quote. Shipping, PCB
minimum order and printing can dominate; combine with an existing order. Buy
only test quantities before proving fit. A full 58-contact build is not yet a
qualified or costed production connector.

## Print and assemble

1. Print all three body variants. The exported body has its open pocket face on
   the bed, bores vertical and screw feet at the top. Keep supports out of bores.
   The front is also exported mating face down; compensate elephant's foot and
   inspect/clear holes without widening the retaining lip. A 0.4 mm FDM
   nozzle is a poor first choice: the thinnest nominal pocket web is 0.37 mm.
   Resin capability and shrinkage still require a sample, not a promised fit.
2. Check a **loose** socket against a sacrificial EFS blade before assembly.
   Reject binding, absent spring grip, scoring or plastic deformation. A circular
   pin rating is not a diagonal-based qualification for a rectangle. If it fails,
   stop this contact branch and select a different spring contact/donor insert.
3. Drop four sockets into a body from its open pocket face, tails toward the PCB.
   The front plate captures the flanges. Align the clipped corner on both pieces
   with `KEY` on the PCB; fit screws through front, body and PCB into the nuts.
   The socket entrance sits 1 mm behind the front surface. Never use the front
   plate as an insertion-depth stop for an unknown EFS pin length.
4. Choose the smallest clearance that lets all sockets settle without force.
   The holder is a clearance fit, **not** the manufacturer's 1.45 mm press-fit
   installation. Screw clamping and soldered tails provide retention. Small axial
   float is intentional; do not fill socket pockets with adhesive or solder.
   Body bores are open through the rear; the flange shoulder takes insertion
   load, avoiding a fragile printed membrane under each socket.
5. Fit PCB with its silkscreen facing the holder. Integral feet leave 0.4 mm under
   the body for pads/fillets. Solder tails from the back, briefly, checking that
   print material does not soften. Wire TP pads as desired. No precision crimp
   tool is required. The PCB has no ground plane or common electrical node.

Nominal tail end is Z=8.37 mm; PCB occupies Z=5.9–7.5 mm, giving 0.87 mm nominal
tail protrusion (0.61 mm with both catalogue length tolerances subtracted).
Board-thickness tolerance and actual seating must still be checked. The maximum
nominal-pocket radial float is 0.175 mm; a large printing-clearance variant is
for calibration, not evidence that this alignment error is acceptable in service.

The fixture has broad fastening ears and **cannot be pushed into a fully
populated EFS male connector**: it would collide with neighbouring pins. Use
loose sacrificial pins held independently, or a separate donor populated only
at the four test positions. Do not cut or bend motherboard pins for this test.
No host insertion-depth stop, keying or 58-contact case clearance is claimed.

## Bench acceptance and next decision

Record dimensions, blade orientation, free insertion length, selected clearance,
printer/material, force, resistance and observations in `measurements.csv`.
Blank cells mean **not measured**. Start with one socket, then all four.

* Confirm each Jn reaches only TPn; all six pairs of channels must remain isolated.
* Compare insertion/withdrawal force with a known-good original contact using
  the same pin. Reject deformation or unstable grip before repeated cycling.
* If a four-wire meter is available, measure contact resistance separately from
  the PCB/wires. The manufacturer's 10 mΩ rating is for its qualified mating
  conditions; it is not a claim for this EFS pairing. A continuity beep alone
  does not qualify a bus connector.
* Try 20 gentle cycles as an initial screen, rechecking movement-sensitive
  continuity, resistance and retention. Passing this screen does not establish
  the original connector's durability rating or a current rating for our print.

Only after this succeeds: choose the contact, measure the host blade depth and
shroud/keying, then extend the insert to 58 positions and design the full adapter.
The original carrier X2 footprint hold stays in force. Making a complete shell
around an unqualified contact now would lock in the riskiest assumption.

## Regenerate and verify

From the repository root, with FreeCAD and KiCad installed:

```sh
FreeCADCmd tools/generate_efs58_coupon_cad.py
/usr/bin/python3 tools/generate_efs58_coupon_pcb.py
python3 tools/draw_efs58_coupon.py
make test-efs58-coupon-cad
make export-efs58-coupon
make test-efs58-coupon
```

On this workstation substitute `/snap/bin/freecad.cmd` for `FreeCADCmd`.
`test-efs58-coupon-cad` means KiCad ERC/DRC/parity; FreeCAD geometry checks run
inside the model generator. Portable tests check released STL topology, dimensions,
channel connectivity, tolerance arithmetic and evidence freshness without CAD tools.

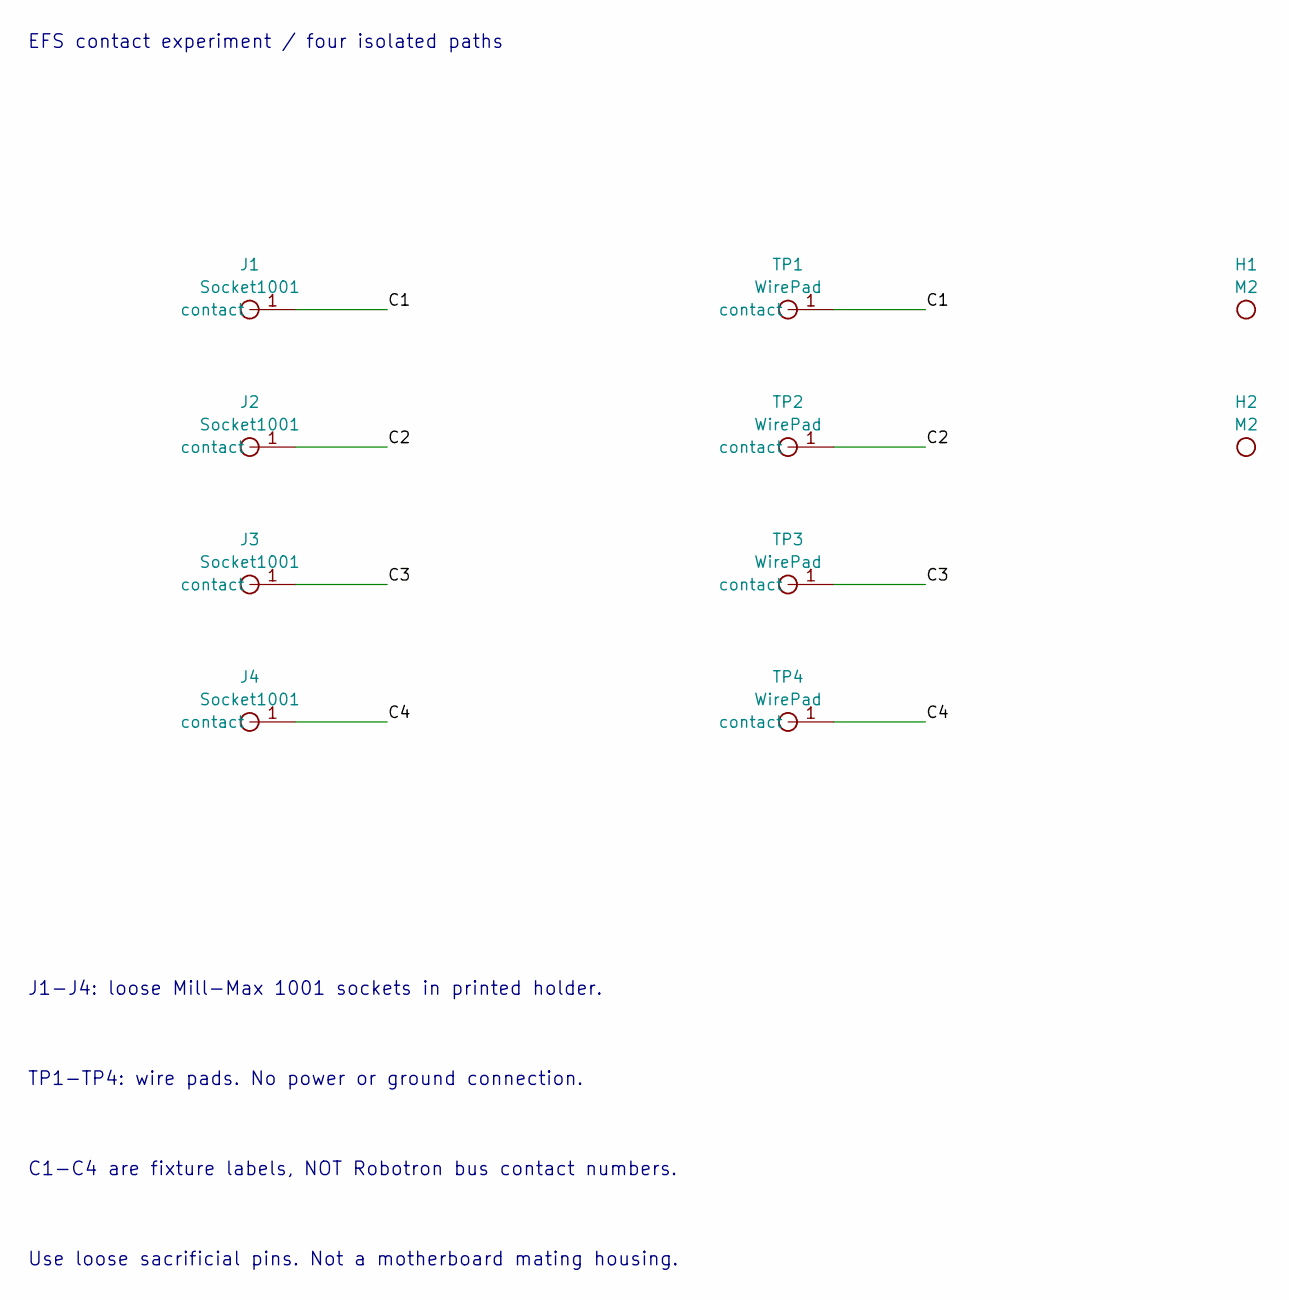
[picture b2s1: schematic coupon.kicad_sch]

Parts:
H1, H2: M2
J1, J2, J3, J4: Socket1001
TP1, TP2, TP3, TP4: WirePad

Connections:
/C1: J1.1, TP1.1
/C2: J2.1, TP2.1
/C3: J3.1, TP3.1
/C4: J4.1, TP4.1

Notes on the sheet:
EFS contact experiment / four isolated paths
J1-J4: loose Mill-Max 1001 sockets in printed holder.
TP1-TP4: wire pads. No power or ground connection.
C1-C4 are fixture labels, NOT Robotron bus contact numbers.
Use loose sacrificial pins. Not a motherboard mating housing.

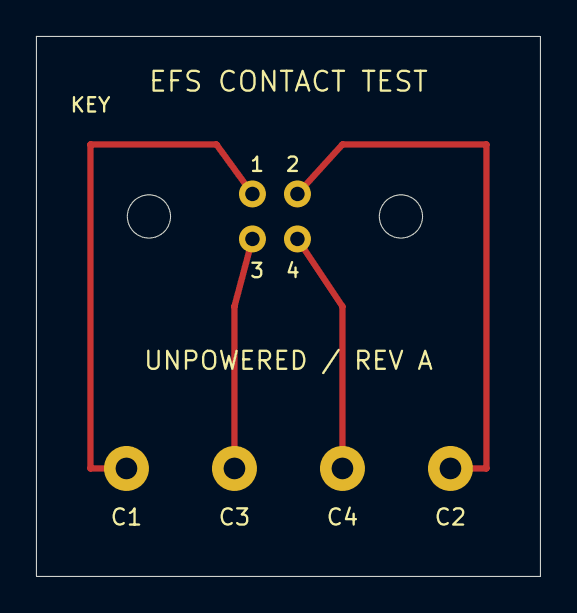
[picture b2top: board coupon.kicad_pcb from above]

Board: 2 copper layers, 28.0 x 30.0 mm, 10 parts (0 on the bottom side), 4 nets.

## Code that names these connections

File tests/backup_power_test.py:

#!/usr/bin/env python3
import copy,json,sys,unittest,xml.etree.ElementTree as ET
from pathlib import Path
ROOT=Path(__file__).resolve().parents[1];sys.path.insert(0,str(ROOT/'tools'))
from check_backup_budget import budget,charge
BASE=ROOT/'hardware/backup-power'
def check(parts,xml):
 by={p['ref']:p for p in parts};pins={(p['ref'],str(n)):net for p in parts for n,_,_,net in p['pins']}
 for net in xml.findall('./nets/net'):
  for node in net.findall('node'):assert '/'+pins[(node.attrib['ref'],node.attrib['pin'])]==net.attrib['name']
 assert [pins[('J3',str(i))] for i in range(1,6)]==['P3V3','GND','SUPPLY_OK','RESERVE_OK','GND']
 for ref,k,a in [('D1','P_VSYS','V5_MODULE'),('D2','CHARGE_IN','V5_MODULE'),('D3','P_VSYS','CAP_FUSED')]:assert [pins[(ref,str(i))] for i in (1,2)]==[k,a]
 assert [pins[('R1',str(i))] for i in (1,2)]==['CHARGE_IN','CAP_TOP'] and by['R1']['value']=='100R_1W_1pct'
 for ref,hi,lo in [('U1','CAP_TOP','CAP_MID'),('U2','CAP_MID','GND')]:assert [pins[(ref,str(i))] for i in (1,2,3)]==[hi,hi,lo]
 for ref,rail in [('U3','SENSE3'),('U4','SENSE4')]:
  assert pins[(ref,'3')]==rail and pins[(ref,'6')]=='P3V3' and pins[(ref,'2')]=='GND'
class Backup(unittest.TestCase):
 def test_contract(self):
  c=json.loads((BASE/'connections.json').read_text());self.assertFalse(c['carrier_integrated']);self.assertFalse(c['fabrication_ready']);xml=ET.parse(BASE/'backup.net.xml');check(c['parts'],xml)
  for ref in ['D1','D2','D3','U1','U2']:
   bad=copy.deepcopy(c['parts']);p=next(p for p in bad if p['ref']==ref);p['pins'][0][3],p['pins'][-1][3]=p['pins'][-1][3],p['pins'][0][3]
   with self.subTest(ref=ref),self.assertRaises(AssertionError):check(bad,xml)
 def test_budget(self):
  p=json.loads((BASE/'budget-inputs.json').read_text());r=budget(p);self.assertLess(r['max_startup_charge_a'],.06)
  self.assertGreater(r['rows'][0]['reserve_s'],r['rows'][-1]['reserve_s']);self.assertFalse(r['rows'][-1]['can_admit_first_sector'])
  p['cell_capacitance_f']=0;self.assertTrue(all(x['reserve_s']==0 for x in budget(p)['rows']))
 def test_mismatch_clamp(self):
  p=json.loads((BASE/'budget-inputs.json').read_text());self.assertLessEqual(max(charge(p)['maximum_cell_v']),2.55);self.assertGreater(max(charge(p,False)['maximum_cell_v']),3)
if __name__=='__main__':unittest.main()
